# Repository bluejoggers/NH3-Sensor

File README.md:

# NH3-Sensor
Contains all files and folders relating to KiCAD

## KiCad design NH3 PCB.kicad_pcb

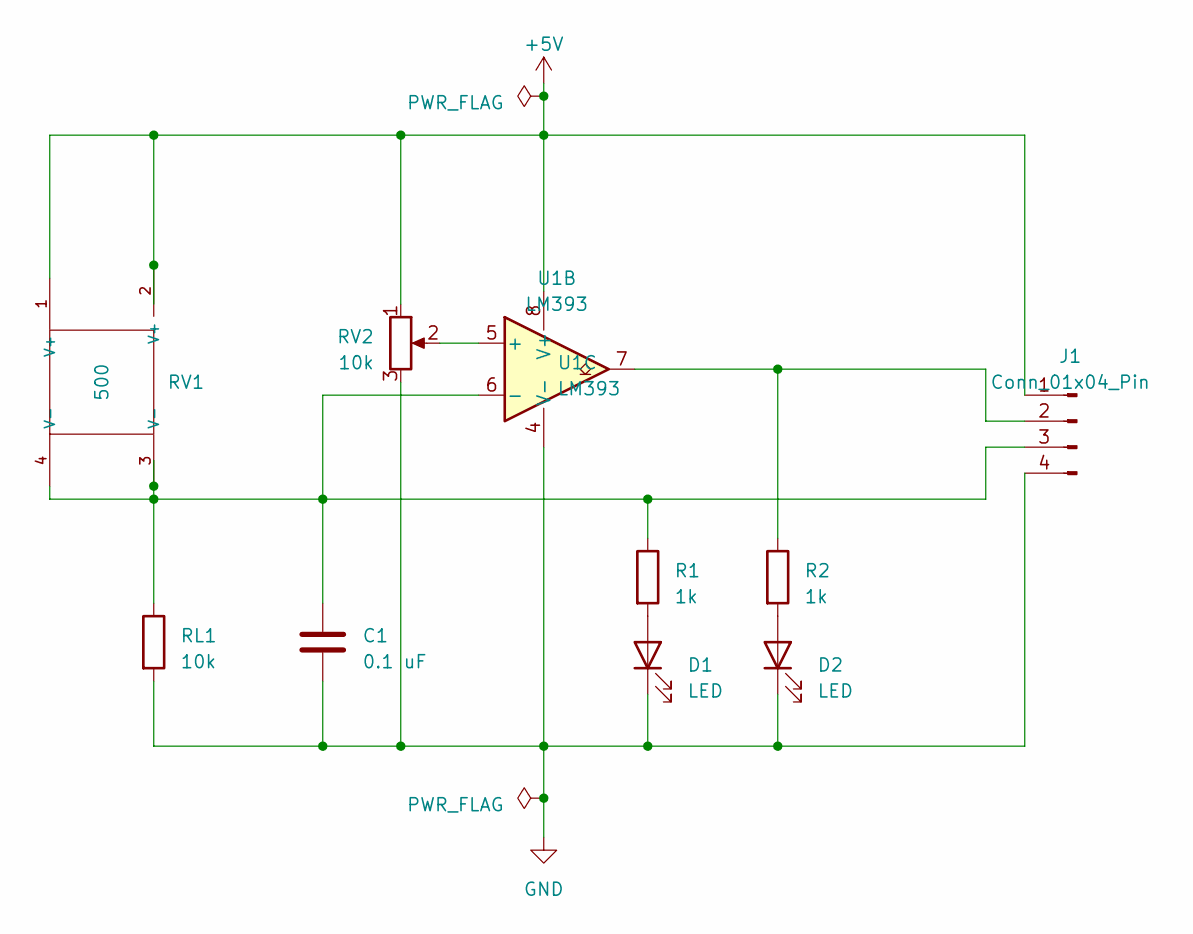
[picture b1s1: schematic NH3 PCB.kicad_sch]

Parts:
C1: 0.1 uF; C_Disc_D5.0mm_W2.5mm_P2.50mm
D1, D2: LED; LED_D5.0mm_Horizontal_O1.27mm_Z3.0mm
J1: Conn_01x04_Pin; PinHeader_1x04_P2.54mm_Horizontal
R1, R2: 1k; R_Axial_DIN0207_L6.3mm_D2.5mm_P7.62mm_Horizontal
RL1: 10k; R_Axial_DIN0207_L6.3mm_D2.5mm_P7.62mm_Horizontal
RV1: 500; NH3Sensor
RV2: 10k; Potentiometer_Bourns_3386X_Horizontal
U1: LM393

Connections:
+5V: J1.1, RV1.1 (V+), RV1.2 (V+), RV2.1, U1.8 (V+)
GND: C1.1, D1.1 (K), D2.1 (K), J1.4, RL1.2, RV2.3, U1.4 (V-)
unnamed: D1.2 (A), R1.2
unnamed: D2.2 (A), R2.2
unnamed: J1.2, R2.1, U1.7
unnamed: C1.2, J1.3, R1.1, RL1.1, RV1.3 (V-), RV1.4 (V-), U1.6 (-)
unnamed: RV2.2, U1.5 (+)

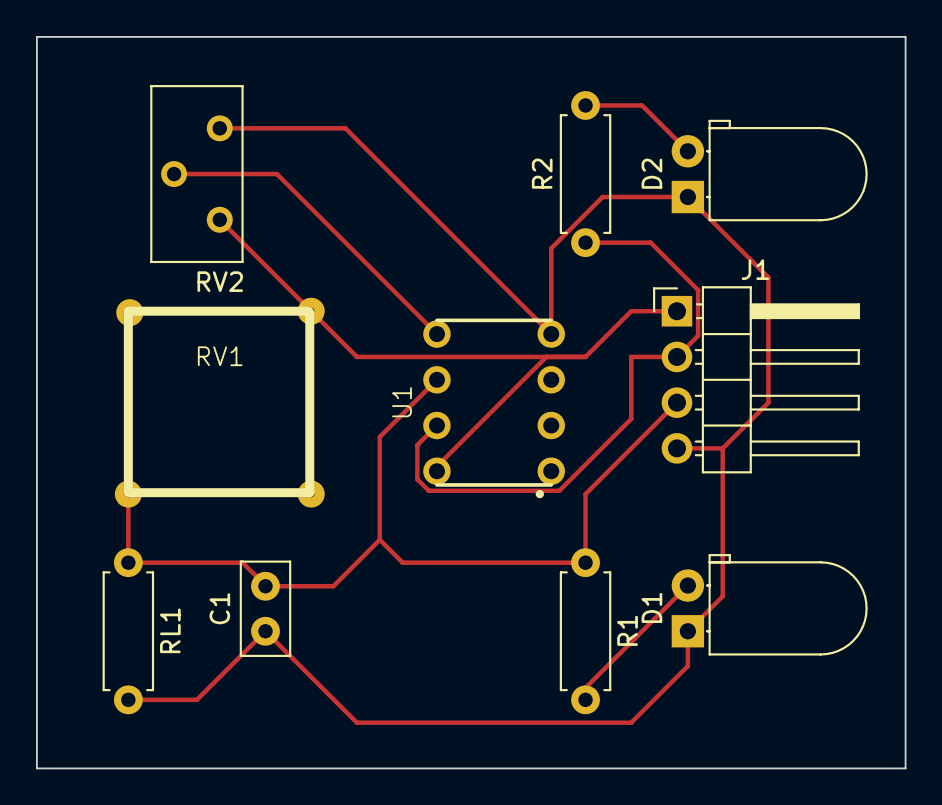
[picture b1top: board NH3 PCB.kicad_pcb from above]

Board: 2 copper layers, 48.3 x 40.6 mm, 10 parts (0 on the bottom side), 7 nets.

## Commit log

2023-04-18 Final Draft for PCB of Ammonia Sensor
